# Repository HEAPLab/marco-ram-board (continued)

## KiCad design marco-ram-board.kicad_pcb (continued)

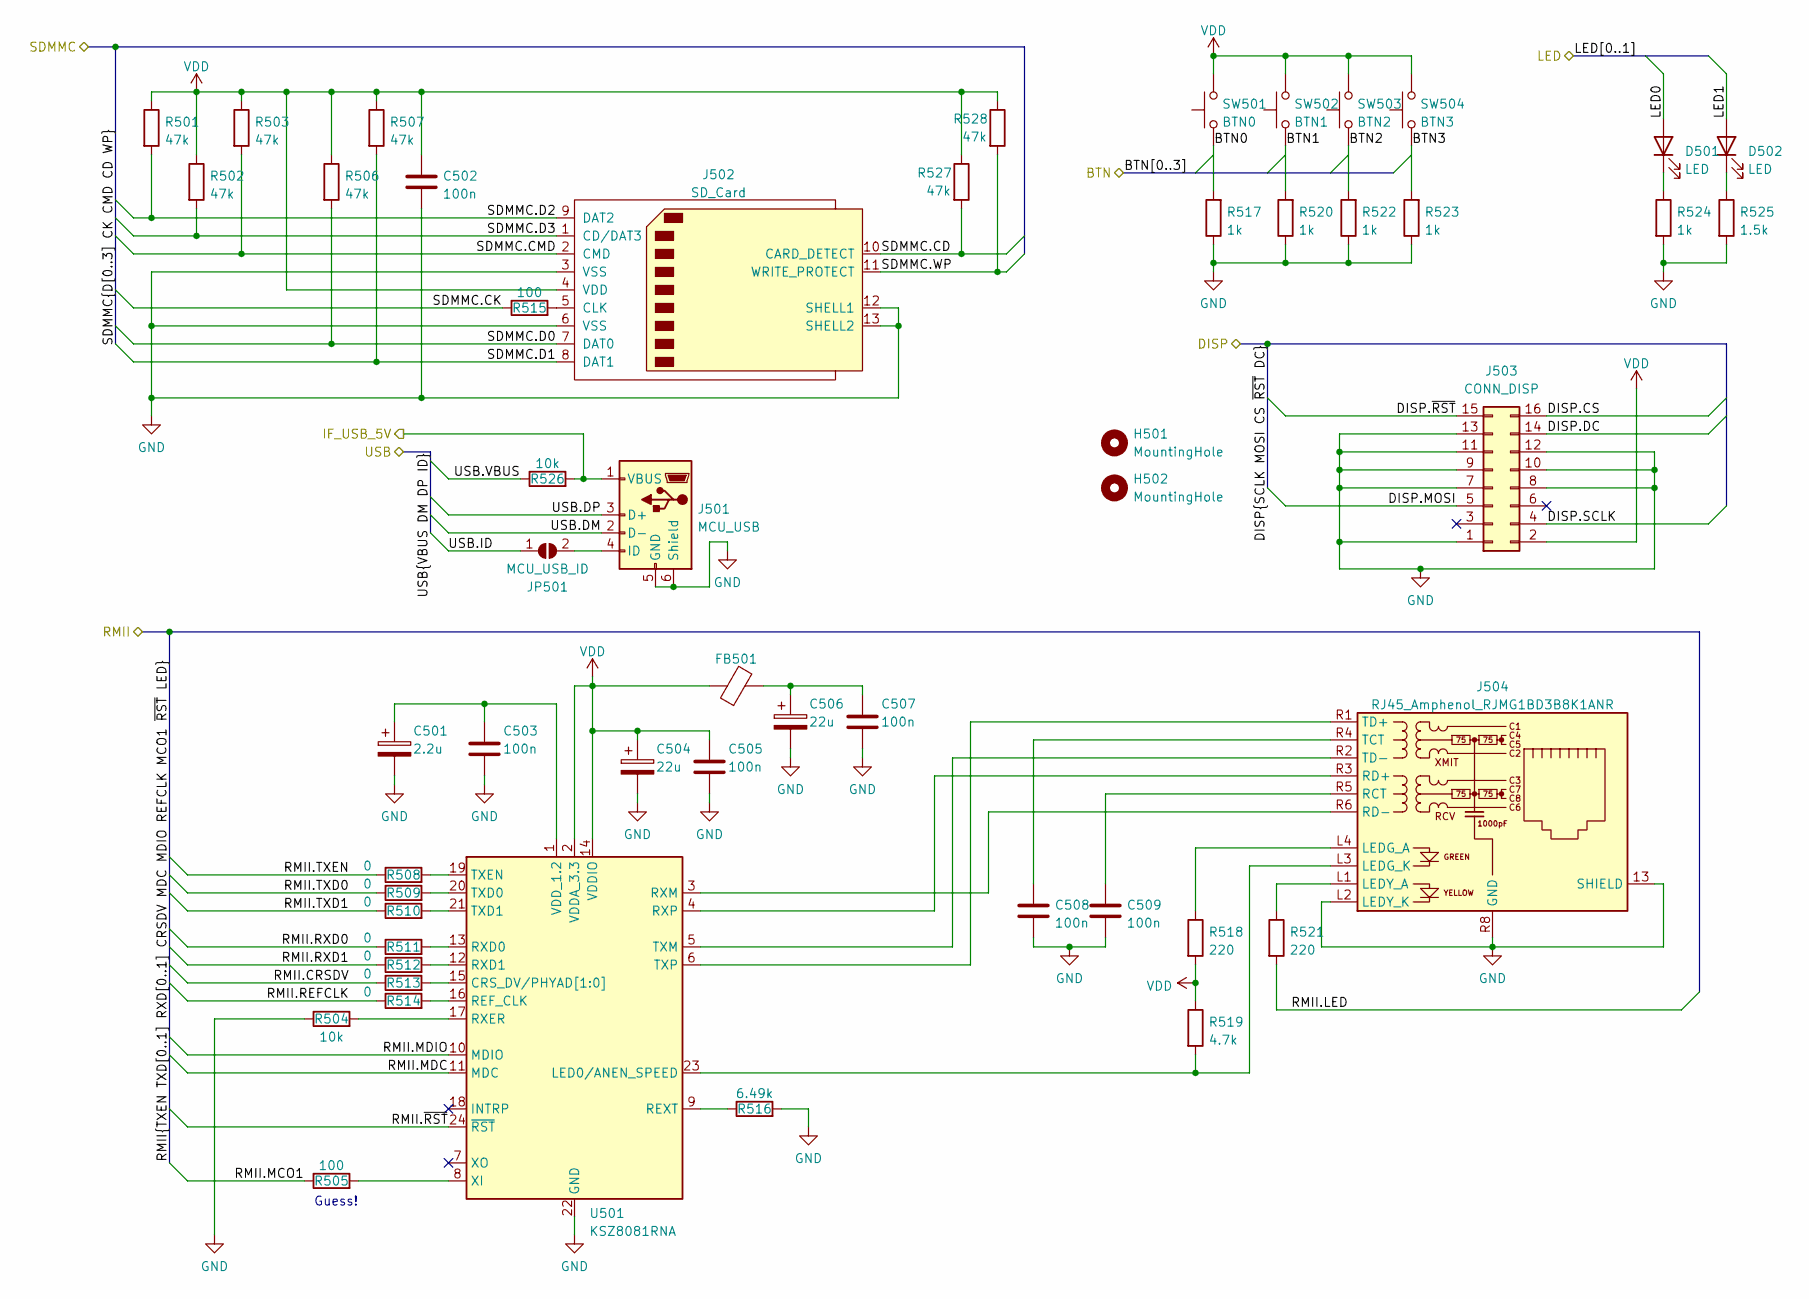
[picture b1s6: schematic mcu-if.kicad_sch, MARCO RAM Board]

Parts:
C501: 2.2u; C_0805_2012Metric_Pad1.18x1.45mm_HandSolder
C502, C503, C505, C507, C508, C509: 100n; C_0603_1608Metric_Pad1.08x0.95mm_HandSolder
C504, C506: 22u; CP_EIA-3216-18_Kemet-A_Pad1.58x1.35mm_HandSolder; Part 74-293D226X96R3A2TE3
D501, D502: LED; LED_PLCC-2_3.4x3.0mm_KA
FB501: FerriteBead; L_0603_1608Metric_Pad1.05x0.95mm_HandSolder; Part 815-ACML-0603H-301
H501, H502: MountingHole; MountingHole_2.7mm_M2.5
J501: MCU_USB; USB_Mini-B_Wuerth_65100516121_Horizontal
J502: SD_Card; SD_Hirose_DM1AA_SF_PEJ82
J503: CONN_DISP; PinSocket_2x08_P2.54mm_Vertical
J504: RJ45_Amphenol_RJMG1BD3B8K1ANR
JP501: MCU_USB_ID; SolderJumper-2_P1.3mm_Open_RoundedPad1.0x1.5mm
R501, R502, R503, R506, R507, R527, R528: 47k; R_0603_1608Metric_Pad0.98x0.95mm_HandSolder
R504, R526: 10k; R_0603_1608Metric_Pad0.98x0.95mm_HandSolder
R505, R515: 100; R_0603_1608Metric_Pad0.98x0.95mm_HandSolder
R508, R509, R510, R511, R512, R513, R514: 0; R_0603_1608Metric_Pad0.98x0.95mm_HandSolder
R516: 6.49k; R_0603_1608Metric_Pad0.98x0.95mm_HandSolder
R517, R520, R522, R523, R524: 1k; R_0603_1608Metric_Pad0.98x0.95mm_HandSolder
R518, R521: 220; R_0603_1608Metric_Pad0.98x0.95mm_HandSolder
R519: 4.7k; R_0603_1608Metric_Pad0.98x0.95mm_HandSolder
R525: 1.5k; R_0603_1608Metric_Pad0.98x0.95mm_HandSolder
SW501: BTN0; DTSMW69N
SW502: BTN1; DTSMW69N
SW503: BTN2; DTSMW69N
SW504: BTN3; DTSMW69N
U501: KSZ8081RNA; QFN-24-1EP_4x4mm_P0.5mm_EP2.6x2.6mm

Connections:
/mcu-if/BTN0: R517.2, SW501.1; also elsewhere on the board
/mcu-if/BTN1: R520.2, SW502.1; also elsewhere on the board
/mcu-if/BTN2: R522.2, SW503.1; also elsewhere on the board
/mcu-if/BTN3: R523.2, SW504.1; also elsewhere on the board
/mcu-if/DISP.CS: J503.16; also elsewhere on the board
/mcu-if/DISP.DC: J503.14; also elsewhere on the board
/mcu-if/DISP.MOSI: J503.5; also elsewhere on the board
/mcu-if/DISP.SCLK: J503.4; also elsewhere on the board
/mcu-if/DISP.~RST: J503.15; also elsewhere on the board
/mcu-if/IF_USB_5V: J501.1 (VBUS), R526.2
/mcu-if/LED0: D501.2 (A); also elsewhere on the board
/mcu-if/LED1: D502.2 (A); also elsewhere on the board
/mcu-if/RMII.CRSDV: R513.1; also elsewhere on the board
/mcu-if/RMII.LED: R521.2; also elsewhere on the board
/mcu-if/RMII.MCO1: R505.1; also elsewhere on the board
/mcu-if/RMII.MDC: U501.11 (MDC); also elsewhere on the board
/mcu-if/RMII.MDIO: U501.10 (MDIO); also elsewhere on the board
/mcu-if/RMII.REFCLK: R514.1; also elsewhere on the board
/mcu-if/RMII.RXD0: R511.1; also elsewhere on the board
/mcu-if/RMII.RXD1: R512.1; also elsewhere on the board
/mcu-if/RMII.TXD0: R509.1; also elsewhere on the board
/mcu-if/RMII.TXD1: R510.1; also elsewhere on the board
/mcu-if/RMII.TXEN: R508.1; also elsewhere on the board
/mcu-if/RMII.~RST: U501.24 (~RST); also elsewhere on the board
/mcu-if/SDMMC.CD: J502.10 (CARD_DETECT), R527.2; also elsewhere on the board
/mcu-if/SDMMC.CK: R515.1; also elsewhere on the board
/mcu-if/SDMMC.CMD: J502.2 (CMD), R503.2; also elsewhere on the board
/mcu-if/SDMMC.D0: J502.7 (DAT0), R506.2; also elsewhere on the board
/mcu-if/SDMMC.D1: J502.8 (DAT1), R507.2; also elsewhere on the board
/mcu-if/SDMMC.D2: J502.9 (DAT2), R501.2; also elsewhere on the board
/mcu-if/SDMMC.D3: J502.1 (CD/DAT3), R502.2; also elsewhere on the board
/mcu-if/SDMMC.WP: J502.11 (WRITE_PROTECT), R528.2; also elsewhere on the board
/mcu-if/USB.DM: J501.2 (D-); also elsewhere on the board
/mcu-if/USB.DP: J501.3 (D+); also elsewhere on the board
/mcu-if/USB.ID: JP501.1 (A); also elsewhere on the board
/mcu-if/USB.VBUS: R526.1; also elsewhere on the board
GND: C501.2, C502.2, C503.2, C504.2, C505.2, C506.2, C507.2, C508.2, C509.2, J501.5 (GND), J501.6 (Shield), J502.3 (VSS), J502.6 (VSS), J502.12 (SHELL1), J502.13 (SHELL2), J503.1, J503.7, J503.8, J503.9, J503.10, J503.11, J503.12, J503.13, J504.13 (SHIELD), J504.L2 (LEDY_K), J504.R8 (GND), R504.1, R516.2, R517.1, R520.1, R522.1, R523.1, R524.2, R525.2, U501.22 (GND), U501.25 (GND); also elsewhere on the board
unnamed: C501.1, C503.1, U501.1 (VDD_1.2)
unnamed: C506.1, C507.1, FB501.2
unnamed: C508.1, J504.R4 (TCT)
unnamed: C509.1, J504.R5 (RCT)
unnamed: D501.1 (K), R524.1
unnamed: D502.1 (K), R525.1
unnamed: J501.4 (ID), JP501.2 (B)
unnamed: J502.5 (CLK), R515.2
unnamed: J504.L1 (LEDY_A), R521.1
unnamed: J504.L3 (LEDG_K), R519.2, U501.23 (LED0/ANEN_SPEED)
unnamed: J504.L4 (LEDG_A), R518.1
unnamed: J504.R1 (TD+), U501.6 (TXP)
unnamed: J504.R2 (TD-), U501.5 (TXM)
unnamed: J504.R3 (RD+), U501.4 (RXP)
unnamed: J504.R6 (RD-), U501.3 (RXM)
unnamed: R504.2, U501.17 (RXER)
unnamed: R505.2, U501.8 (XI)
unnamed: R508.2, U501.19 (TXEN)
unnamed: R509.2, U501.20 (TXD0)
unnamed: R510.2, U501.21 (TXD1)
unnamed: R511.2, U501.13 (RXD0)
unnamed: R512.2, U501.12 (RXD1)
unnamed: R513.2, U501.15 (CRS_DV/PHYAD[1:0])
unnamed: R514.2, U501.16 (REF_CLK)
unnamed: R516.1, U501.9 (REXT)
VDD: C502.1, C504.1, C505.1, FB501.1, J502.4 (VDD), J503.2, R501.1, R502.1, R503.1, R506.1, R507.1, R518.2, R519.1, R527.1, R528.1, SW501.2, SW502.2, SW503.2, SW504.2, U501.2 (VDDA_3.3), U501.14 (VDDIO); also elsewhere on the board

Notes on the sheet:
Guess!

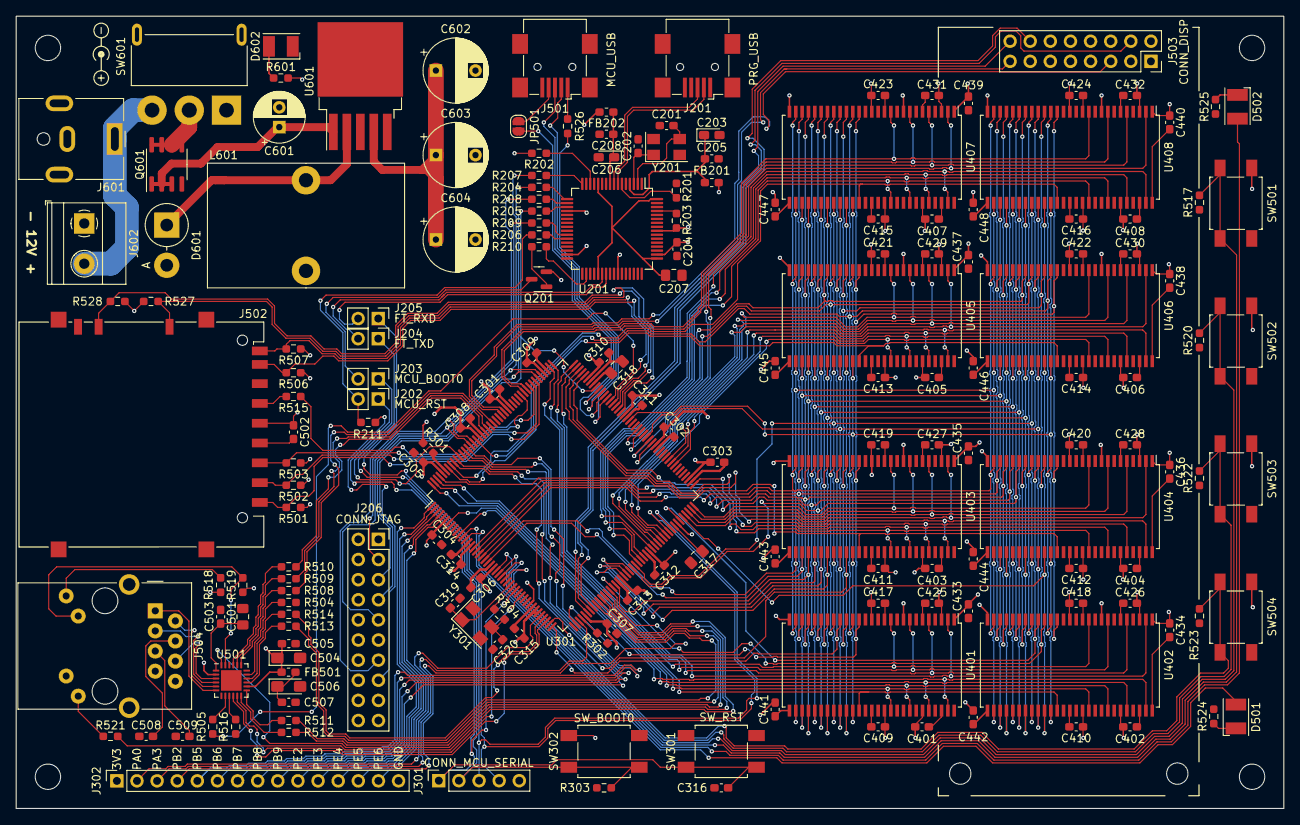
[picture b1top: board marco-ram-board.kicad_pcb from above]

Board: 4 copper layers, 160.0 x 100.0 mm, 185 parts (0 on the bottom side), 179 nets.

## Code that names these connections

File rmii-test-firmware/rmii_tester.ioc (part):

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Mcu.Name=STM32F765I(G-I)Tx
Mcu.Package=LQFP176
Mcu.UserName=STM32F765IITx
PA1.Mode=RMII
PA1.Signal=ETH_REF_CLK
PA2.Mode=RMII
PA2.Signal=ETH_MDIO
PA7.Mode=RMII
PA7.Signal=ETH_CRS_DV
PA8.Mode=Clock-out-1
PA8.Signal=RCC_MCO_1
PB0.Signal=GPIO_Output
PB1.Signal=GPIO_Output
PB10.Mode=Asynchronous
PB10.Signal=USART3_TX
PB11.Mode=Asynchronous
PB11.Signal=USART3_RX
PC1.Mode=RMII
PC1.Signal=ETH_MDC
PC4.Mode=RMII
PC4.Signal=ETH_RXD0
PC5.Mode=RMII
PC5.Signal=ETH_RXD1
PG11.Mode=RMII
PG11.Signal=ETH_TX_EN
PG13.Mode=RMII
PG13.Signal=ETH_TXD0
PG14.Mode=RMII
PG14.Signal=ETH_TXD1
PH0/OSC_IN.Mode=HSE-External-Oscillator
PH0/OSC_IN.Signal=RCC_OSC_IN
PH1/OSC_OUT.Mode=HSE-External-Oscillator
PH1/OSC_OUT.Signal=RCC_OSC_OUT
RCC.HSE_VALUE=25000000
RCC.SYSCLKFreq_VALUE=216000000
RCC.SYSCLKSource=RCC_SYSCLKSOURCE_PLLCLK
board=custom

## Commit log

2023-02-11 Initial design primarily done by Federico Terraneo.
2023-02-11 Add datasheets of currently used components.
2023-02-11 Complete wiring of SDRAM.
2023-02-12 Add SD card connector.
2023-02-12 Some minor repositioning.
2023-02-14 Add power supply.
2023-02-14 Add MCU USB
2023-02-25 More capacitors for PSU
2023-02-25 Configured PCB sizes for either eurocircuits or pcbway
2023-02-25 Screenshot of board configuration
2023-02-25 Power supply design fine tuning
2023-02-25 Add Ethernet interface.
2023-02-25 Capacitor part assignment
2023-02-25 Add display connector
2023-02-25 Add extension connector, LEDs, buttons
2023-02-25 Led datasheets
2023-02-25 Final annotate pass
2023-02-25 ERC pass
2023-02-25 Re-annotation, footprints
2023-02-25 Add button footprint
2023-02-26 More footprints
2023-02-26 Power switch footprint.
    This is the last footprint!
2023-03-02 Also connect MCU USB VBUS and ID.
    Useful for detecting disconnections.
2023-03-02 Move programming USART to USART3 from USART1 because the pins configured by the bootloader on USART1 are now occupied.
2023-03-02 Disconnect USB ID pin by default, add a solder bridge to allow reconnecting if needed.
2023-03-12 Fix led current limiting resistor values.
2023-03-12 Started placement
2023-03-12 Placement almost complete
2023-03-12 Removed marker added by mistake
2023-03-13 Fix several footprints, adjust pcb layout.
    - Change footprint for power switch, add the switch's datasheet.
    - Rearrange power supply area of PCB to make new switch fit.
    - Fix SD card socket footprint to be compatible with the schematic symbol. Add its datasheet
    - Add pullups for SD card socket WP and CD (fixed footprint hardwires one side of the switches to GND)
    - Add datasheet for the barrel jack.
2023-03-13 Fix overlapped label on DRAM data bus causing D16 and D18 nets to be connected together.
2023-03-20 Finish placement, start routing.
2023-03-20 Small placement modifications, change most routing to .2mm, more RAM routing
2023-03-21 Finish RAM routing (except connections to MCU).
2023-03-25 Add worksheet template with PoliMi logo.
2023-03-25 Fix double connection on the SDRAM bus.
2023-03-25 Reduce size of logo polygon.
2023-04-02 Route power supply
2023-04-02 Update layout from schematic to propagate effects of commit b3d85d6.
2023-04-17 Fix missing connections in SDRAM.
2023-04-17 Bring out all SDRAM BUS elements from the SDRAM section from the closest point to the MCU
2023-04-17 Route SDRAM. Whew!
2023-04-19 SDRAM routing cleanup
2023-04-19 Add HEAPLab logos.
2023-04-19 More net classes
2023-04-19 MCU USB
2023-04-19 More SDRAM routing cleanup, partial screen/buttons routing
2023-04-20 Screen/buttons/LEDs routing
2023-04-21 Properly set unconnected tag on unused MCU pins
2023-04-21 Use 0.15mm track width for all signals, not just the SDRAM.
2023-04-21 Route SDMMC
2023-04-21 Route debug JTAG and serial.
2023-04-21 Artwork cleanup
2023-04-23 Fix missing EXT9 connection, move EXT9-13 to PEx, route EXT connector.
2023-04-23 Add names to Ext connector pins.
2023-04-23 Route RMII.
2023-04-23 Route VDD.
2023-04-23 Finishing touches.
2023-04-24 Add additional silkscreen items, add 3D models for power switch.
2023-05-07 Delay line for SDRAM CLK.
2023-05-07 Keepout zones under unregulated voltage and clock oscillator.
2023-05-13 Add Miosix logo
2023-05-14 Minor track cleanup
2023-05-20 Remove keepout under crystal
2023-07-01 Fix C501 symbol, it is a non polarized ceramic
2023-07-01 Fix ferrite bead from the wrong side
2023-07-01 Fix base resistor value
2023-07-01 BON consolidation
2023-07-01 BOM consolidations
2023-07-01 Gerber
2023-09-15 Update gerbers and gerber generation options per JLCPCB's guidelines.
2023-09-15 Add board specification file for JLCPCB.
2023-09-28 Fully update PCB and schematic after BOM consolidation
2023-09-28 Move labels on switches, jumpers and so on to a separate Label property from the Value property.
    Value must be the same for components that are physically the same, otherwise it screws up the BOM. But that means we need to add each label manually.
2023-09-28 Generate interactive BOM
2023-09-28 Move BOM .ods to the bom directory
2023-09-28 Add PDF schematic
2023-12-23 Add source code of RMII test firmware for the board.
2023-12-23 RMII test program: Increase usefulness of logs
